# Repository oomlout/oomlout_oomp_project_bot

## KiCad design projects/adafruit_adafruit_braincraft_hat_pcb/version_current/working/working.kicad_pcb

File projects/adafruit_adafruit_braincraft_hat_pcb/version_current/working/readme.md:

# OOMP Project  
## Adafruit-BrainCraft-HAT-PCB  by adafruit  
  
oomp key: oomp_projects_flat_adafruit_adafruit_braincraft_hat_pcb  
(snippet of original readme)  
  
-- Adafruit Adafruit BrainCraft HAT - Machine Learning for Raspberry Pi 4 PCB  
  
<a href="http://www.adafruit.com/products/4374"><br/>  
Click here to purchase one from the Adafruit shop</a>  
  
PCB files for the Adafruit BrainCraft HAT - Machine Learning for Raspberry Pi 4.   
  
Format is EagleCAD schematic and board layout  
* https://www.adafruit.com/product/4374  
  
--- Description  
  
The idea behind the BrainCraft HAT is that you’d be able to “craft brains” for Machine Learning on the EDGE, with Microcontrollers & Microcomputers. On ASK AN ENGINEER, our founder & engineer chatted with Pete Warden, the technical lead of the mobile, embedded TensorFlow Group on Google’s Brain team about what would be ideal for a board like this.  
  
And here’s what we designed! The BrainCraft HAT has a 240×240 TFT IPS display for inference output, slots for camera connector cable for imaging projects, a 5 way joystick and button for UI input, left and right microphones, stereo headphone out, stereo 1 W speaker out, three RGB DotStar LEDs, two 3 pin STEMMA connectors on PWM pins so they can drive NeoPixels or servos, and Grove/STEMMA/Qwiic I2C port. This will let people build a wide range of audio/video AI projects while also allowing easy plug-in of sensors and robotics!  
  
A controllable mini fan attaches to the bottom, and can be used to keep your Pi cool while doing intense AI inference calculations. **Most importantly, there’s an On/Off switch that will comp  
  full source readme at [readme_src.md](readme_src.md)  
  
source repo at: [https://github.com/adafruit/Adafruit-BrainCraft-HAT-PCB](https://github.com/adafruit/Adafruit-BrainCraft-HAT-PCB)  
## Board  

## Schematic  

[schematic pdf](working_schematic.pdf)  
## Images

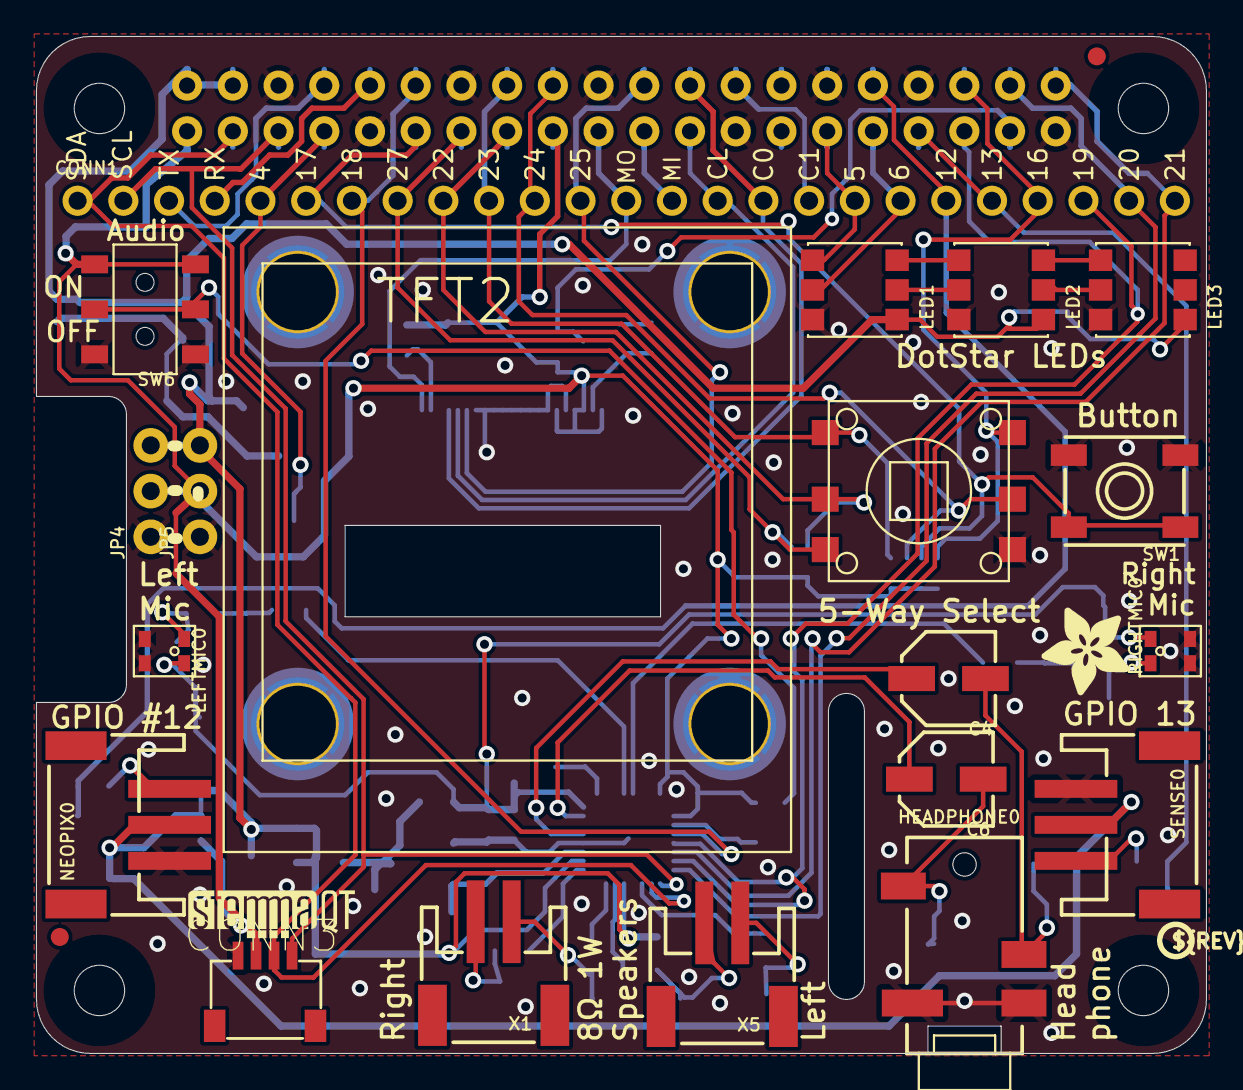
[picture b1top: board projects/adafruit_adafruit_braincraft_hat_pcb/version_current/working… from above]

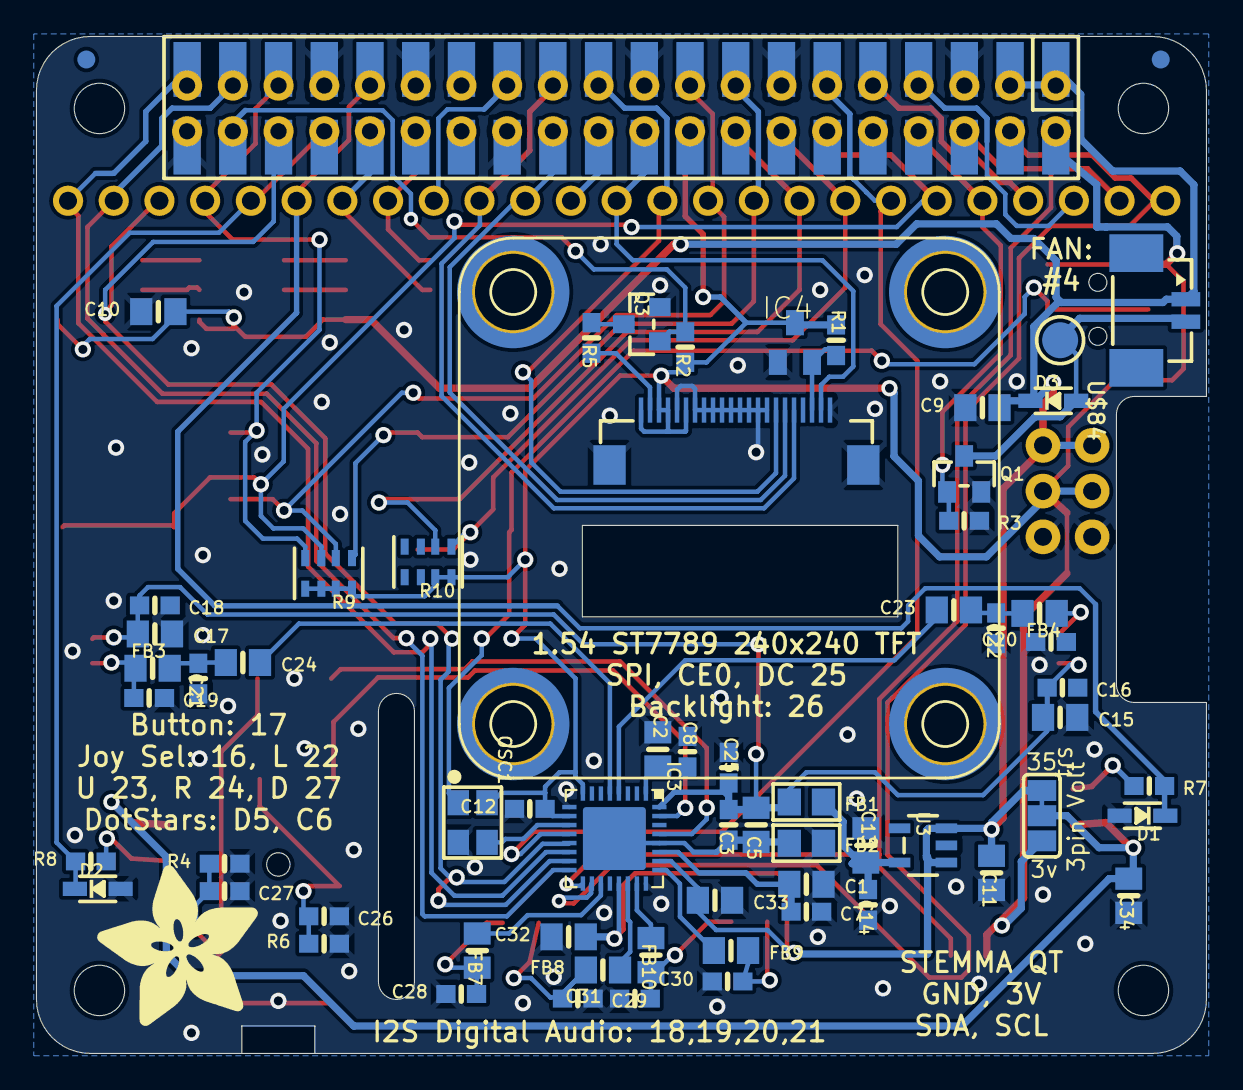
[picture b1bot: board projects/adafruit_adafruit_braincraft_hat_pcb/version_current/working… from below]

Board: 2 copper layers, 65.0 x 56.5 mm, 95 parts (69 on the bottom side), 67 nets.

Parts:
C1, C2, C5, C9, C10, C11, C13, C15, C17, C23, C24, C32, C33, C34: 10uF; 0805-NO
C3, C7, C8, C12, C14, C16, C18, C25: 0.1uF; 0603-NO
C4, C6: 100uF; PANASONIC_C
C19, C20, C21, C22: 33pF; 0603-NO
C26, C27: 220pF; 0603-NO
C28, C29, C30, C31: 100pF; 0603-NO
CONN1: HEADER-1X25; 1X25_ROUND_70MIL
CONN3: STEMMA_I2C_QT; JST_SH4
D1, D2: 3.6V; SOD-323
D3: 1N4148; SOD-323
FB1, FB2: Ferrite; 0805
FB3, FB7, FB8, FB9, FB10: Ferrite; 0805-NO
FB4: FERRITE; 0805-NO
FID1, FID2: FIDUCIAL_1MM
HEADPHONE0: 4UCONN_18510
IC3: WM8960; QFN32_5MM
IC4: APX803-SAG; SOT23
JP4, JP5: 1X03_ROUND_76
LED1, LED2, LED3: SK6822; APA102
LEFTMIC0: SPW2430HR5H-B
NEOPIX0: JST PH 3; JSTPH3
OSC1: ECS-3225MV; OSC_3.2X2.5MM
Q1, Q3: BSS138; SOT23-WIDE
R1, R2, R3, R4: 10K; 0603-NO
R5: 10; 0603-NO
R6: 10k; 0603-NO
R7, R8: 1K; 0603-NO
R9, R10: 10K; RESPACK_4X0603
RIGHTMIC0: SPW2430HR5H-B
RPI1: RASPBERRYPI_BPLUS_HAT_SMTTHM_SLOTS; PI_HAT_SMTTHM_SLOTS
SENSE0: JST PH 3; JSTPH3
SJ1: SOLDERJUMPER_2WAY_OPEN_NOPASTE
SW1: EVQQ; EVQ-Q2_SMALLER
SW5: NAVSWITCHSKQUABAUE010; SKQUBAE010
SW6: EG1390
TFT2: DISP_TFT_1.54IN_240X240_22P; TFT_1.54IN_240X240_22PIN
TP1, TP2, TP3, TP4: SEWTAP_SMTNUTM3; SMT_NUT_3MM
TP6: TESTPOINT_ROUND_2MM
U3: AP2112-3.3K; SOT23-5
U$11: PCBFEAT-REV-040
U$72: STEMMAQT
U$75: ADAFRUIT_5MM
U$79: BRAINPAD_1IN
U$82: FAN_30X30MM
U$84: CON_MOLEX_2P; 53398-0271
U$87: ADAFRUIT_9MM
X1, X5: JSTPH 2P; JSTPH2

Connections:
3.3V: C12.1, CONN3.2, IC3.8, IC3.10, IC4.3, JP4.2, JP5.2, OSC1.4, R1.2, R2.2, R9.5, R9.6, R9.7, R9.8, R10.7, R10.8, RPI1.1, RPI1.17, RPI1.S1, RPI1.S17, SJ1.3, SW6.S1, SW6.S2, TFT2.1, TFT2.3, TFT2.4, TFT2.6
5.0V: C9.1, C10.1, C11.1, C32.1, C33.1, D3.C, IC3.21, IC3.26, JP4.3, JP5.3, LED1.4, LED2.4, LED3.4, RPI1.2, RPI1.4, RPI1.S2, RPI1.S4, SJ1.1, U3.1, U3.3, U$84.1
AGND: C3.2, C5.2, FB2.1, IC3.28, IC3.33
AVDD: C3.1, C5.1, C15.1, C16.1, C17.1, C18.1, C25.1, FB1.1, IC3.32, LEFTMIC0.4, RIGHTMIC0.4
BUTTON: CONN1.6, R9.3, RPI1.11, RPI1.S11, SW1.B, SW1.B'
EECLK: RPI1.28, RPI1.S28
EEDATA: RPI1.27, RPI1.S27
FAN: CONN1.5, Q1.1, R3.1, RPI1.7, RPI1.S7
GND: C1.2, C2.2, C7.2, C8.2, C9.2, C10.2, C11.2, C12.2, C13.2, C14.2, C15.2, C16.2, C17.2, C18.2, C19.2, C20.2, C21.2, C22.2, C25.2, C26.2, C27.2, C28.2, C29.2, C30.2, C31.2, C32.2, C33.2, C34.2, CONN3.1, D1.A, D2.A, FB2.2, HEADPHONE0.1-GND, HEADPHONE0.4-INNER_SLEEVE, IC3.9, IC3.20, IC3.24, IC4.1, JP4.1, JP5.1, LED1.3, LED2.3, LED3.3, LEFTMIC0.2, LEFTMIC0.3, NEOPIX0.1, OSC1.2, Q1.2, Q3.2, R3.2, R4.1, R6.1, RIGHTMIC0.2, RIGHTMIC0.3, RPI1.6, RPI1.9, RPI1.14, RPI1.20, RPI1.25, RPI1.30, RPI1.34, RPI1.39, RPI1.S6, RPI1.S9, RPI1.S14, RPI1.S20, RPI1.S25, RPI1.S30, RPI1.S34, RPI1.S39, SENSE0.1, SW1.A, SW1.A', SW5.4, SW6.O1, SW6.O2, TFT2.5, TFT2.7, TFT2.8, TFT2.9, TFT2.10, TFT2.11, TFT2.12, TFT2.13, TFT2.14, TFT2.15, TFT2.22, TFT2.SUPPORT1, TFT2.SUPPORT2, TP1.P$1, TP2.P$1, TP3.P$1, TP4.P$1, U3.2
I2S_BCLK: CONN1.7, IC3.12, RPI1.12, RPI1.S12
I2S_DIN: CONN1.24, IC3.16, RPI1.38, RPI1.S38
I2S_DOUT: CONN1.25, IC3.14, RPI1.40, RPI1.S40
I2S_LRCLK: CONN1.23, IC3.13, IC3.15, RPI1.35, RPI1.S35
JOY_D: CONN1.8, R10.1, RPI1.13, RPI1.S13, SW5.3
JOY_IN: CONN1.22, R9.4, RPI1.36, RPI1.S36, SW5.6
JOY_L: CONN1.9, R10.2, RPI1.15, RPI1.S15, SW5.2
JOY_R: CONN1.11, R9.2, RPI1.18, RPI1.S18, SW5.5
JOY_U: CONN1.10, R9.1, RPI1.16, RPI1.S16, SW5.1
LEDC: CONN1.19, LED1.2, RPI1.31, RPI1.S31
LEDD: CONN1.18, LED1.1, RPI1.29, RPI1.S29
LEDK: R5.2, TFT2.2
LINPUT1: C23.2, IC3.4
LITE: Q3.1, R2.1, RPI1.37, RPI1.S37
LSTEMMA: NEOPIX0.3, R7.1
MCLK: IC3.11, OSC1.3
MCLK_EN: OSC1.1, SW6.P1, SW6.P2
MICBIAS: C2.1, C8.1, IC3.1
unnamed: FB7.1, IC3.19
unnamed: FB8.1, IC3.22
unnamed: C6.+, IC3.31
unnamed: Q3.3, R5.1
unnamed: C4.+, IC3.29
unnamed: LED1.6, LED2.1
unnamed: C4.-, C27.1, HEADPHONE0.3-OUTER_SLEEVE, R4.2
unnamed: C6.-, C26.1, HEADPHONE0.2-TIP, R6.2
unnamed: LED1.5, LED2.2
unnamed: C19.1, FB3.1, RIGHTMIC0.1
unnamed: C20.1, FB4.1, LEFTMIC0.1
unnamed: LED2.6, LED3.1
unnamed: LED2.5, LED3.2
unnamed: C21.1, C24.1, FB3.2
unnamed: C22.1, C23.1, FB4.2
unnamed: D3.A, Q1.3, TP6.P$1, U$84.2
unnamed: FB9.1, IC3.25
unnamed: FB10.1, IC3.23
OUT: C13.1, C14.1, FB1.2, U3.5
PWM0: CONN1.20, D1.C, R7.2, RPI1.32, RPI1.S32
PWM1: CONN1.21, D2.C, R8.2, RPI1.33, RPI1.S33
RINPUT1: C24.2, IC3.5
RSTEMMA: R8.1, SENSE0.3
RXD: CONN1.4, RPI1.10, RPI1.S10
SCL: CONN1.2, CONN3.4, IC3.17, RPI1.5, RPI1.S5
SDA: CONN1.1, CONN3.3, IC3.18, RPI1.3, RPI1.S3
SPI_CE1: CONN1.17, RPI1.26, RPI1.S26
SPI_MISO: CONN1.14, RPI1.21, RPI1.S21
SPK_LN: C31.1, FB10.2, X1.1
SPK_LP: C30.1, FB9.2, X1.2
SPK_RN: C28.1, FB7.2, X5.1
SPK_RP: C29.1, FB8.2, X5.2
TFT_CS: CONN1.16, RPI1.24, RPI1.S24, TFT2.18
TFT_DC: CONN1.12, RPI1.22, RPI1.S22, TFT2.16
TFT_MOSI: CONN1.13, RPI1.19, RPI1.S19, TFT2.21
TFT_RESET: IC4.2, R1.1, TFT2.20
TFT_SCLK: CONN1.15, RPI1.23, RPI1.S23, TFT2.17
TXD: CONN1.3, RPI1.8, RPI1.S8
VCC: C34.1, NEOPIX0.2, SENSE0.2, SJ1.2
VMID: C1.1, C7.1, IC3.27

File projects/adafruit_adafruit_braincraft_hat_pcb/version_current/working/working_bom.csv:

"Id";"Designator";"Footprint";"Quantity";"Designation";"Supplier and ref";
1;"FID2,FID1";"FIDUCIAL_1MM";2;"FIDUCIAL_1MM";;;
2;"LED1,LED3,LED2";"APA102";3;"SK6822";;;
3;"JP4,JP5";"1X03_ROUND_76";2;"";;;
4;"TFT2";"TFT_1.54IN_240X240_22PIN";1;"DISP_TFT_1.54IN_240X240_22P";;;
5;"SW5";"SKQUBAE010";1;"NAVSWITCHSKQUABAUE010";;;
6;"NEOPIX0,SENSE0";"JSTPH3";2;"JST PH 3";;;
7;"X1,X5";"JSTPH2";2;"JSTPH 2P";;;
8;"C4,C6";"PANASONIC_C";2;"100uF";;;
9;"CONN1";"1X25_ROUND_70MIL";1;"HEADER-1X25";;;
10;"HEADPHONE0";"4UCONN_18510";1;"";;;
11;"SW1";"EVQ-Q2_SMALLER";1;"EVQQ";;;
12;"LEFTMIC0,RIGHTMIC0";"SPW2430HR5H-B";2;"";;;
13;"U$11";"PCBFEAT-REV-040";1;"";;;
14;"U$75";"ADAFRUIT_5MM";1;"";;;
15;"SW6";"EG1390";1;"EG1390";;;
16;"RPI1";"PI_HAT_SMTTHM_SLOTS";1;"RASPBERRYPI_BPLUS_HAT_SMTTHM_SLOTS";;;
17;"U$72";"STEMMAQT";1;"";;;
18;"CONN3";"JST_SH4";1;"STEMMA_I2C_QT";;;
19;"C32,C17,C5,C15,C24,C9,C2,C33,C23,C11,C1,C10,C34,C13";"0805-NO";14;"10uF";;;
20;"U$87";"ADAFRUIT_9MM";1;"";;;
21;"R10,R9";"RESPACK_4X0603";2;"10K";;;
22;"OSC1";"OSC_3.2X2.5MM";1;"ECS-3225MV";;;
23;"C20,C21,C22,C19";"0603-NO";4;"33pF";;;
24;"C30,C28,C29,C31";"0603-NO";4;"100pF";;;
25;"FB10,FB7,FB8,FB3,FB9";"0805-NO";5;"Ferrite";;;
26;"FB2,FB1";"0805";2;"Ferrite";;;
27;"D3";"SOD-323";1;"1N4148";;;
28;"C14,C8,C25,C16,C12,C7,C18,C3";"0603-NO";8;"0.1uF";;;
29;"TP3,TP1,TP2,TP4";"SMT_NUT_3MM";4;"SEWTAP_SMTNUTM3";;;
30;"R6";"0603-NO";1;"10k";;;
31;"Q3,Q1";"SOT23-WIDE";2;"BSS138";;;
32;"R4,R1,R2,R3";"0603-NO";4;"10K";;;
33;"D1,D2";"SOD-323";2;"3.6V";;;
34;"C26,C27";"0603-NO";2;"220pF";;;
35;"IC3";"QFN32_5MM";1;"WM8960";;;
36;"R5";"0603-NO";1;"10";;;
37;"U$79";"BRAINPAD_1IN";1;"";;;
38;"FB4";"0805-NO";1;"FERRITE";;;
39;"IC4";"SOT23";1;"APX803-SAG";;;
40;"SJ1";"SOLDERJUMPER_2WAY_OPEN_NOPASTE";1;"";;;
41;"U$82";"FAN_30X30MM";1;"";;;
42;"U3";"SOT23-5";1;"AP2112-3.3K";;;
43;"TP6";"TESTPOINT_ROUND_2MM";1;"";;;
44;"R8,R7";"0603-NO";2;"1K";;;
45;"U$84";"53398-0271";1;"CON_MOLEX_2P";;;

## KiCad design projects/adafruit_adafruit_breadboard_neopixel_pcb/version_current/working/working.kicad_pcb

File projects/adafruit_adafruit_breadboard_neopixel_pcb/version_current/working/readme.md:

# Adafruit_Breadboard_NeoPixel_PCB by adafruit  
This is a harvested standardized copy of a project from github.  
The original project can be found at:  
https://github.com/adafruit/Adafruit_Breadboard_NeoPixel_PCB  
Please consult that link for additional, details, files, and license information.  
Note: It was auto harvested and if the original repo had more than one board file or anything out of the ordinary the files here are likely not representative.

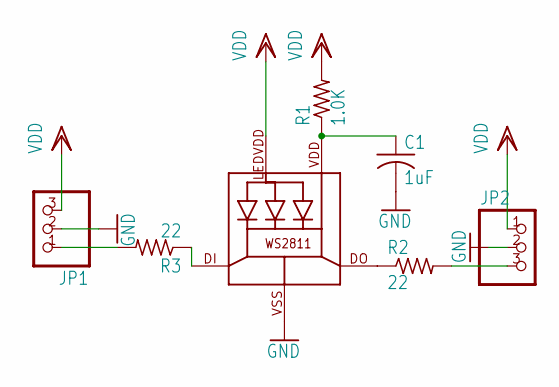
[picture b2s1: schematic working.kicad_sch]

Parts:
C1: 1uF; C0603K
JP1, JP2: PINHD-1X3CB; 1X03-CLEANBIG
LED1: WS28115050
R1: 1.0K; R0603
R2, R3: 22; R0603

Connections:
GND: C1.2, JP1.2, JP2.2, LED1.VSS (GND)
IN: JP1.1, R3.2
unnamed: LED1.DO, R2.1
unnamed: LED1.DI, R3.1
unnamed: C1.1, LED1.VDD, R1.1
OUT: JP2.3, R2.2
VDD: JP1.3, JP2.1, LED1.LEDVDD, R1.2

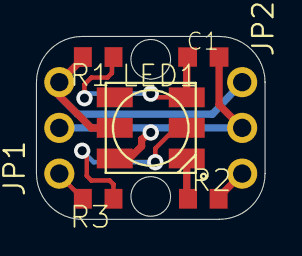
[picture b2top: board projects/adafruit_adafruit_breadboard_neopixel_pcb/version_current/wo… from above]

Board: 16 copper layers, 12.7 x 10.2 mm, 10 parts (1 on the bottom side), 7 nets.

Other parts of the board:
@HOLE0, @HOLE1: (no value)
U$1: ADAFRUIT_2.5MM

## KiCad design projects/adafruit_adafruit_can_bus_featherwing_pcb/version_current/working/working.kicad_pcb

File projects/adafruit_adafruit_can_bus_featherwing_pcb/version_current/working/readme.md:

# Adafruit-CAN-Bus-FeatherWing-PCB by adafruit  
This is a harvested standardized copy of a project from github.  
The original project can be found at:  
https://github.com/adafruit/Adafruit-CAN-Bus-FeatherWing-PCB  
Please consult that link for additional, details, files, and license information.  
Note: It was auto harvested and if the original repo had more than one board file or anything out of the ordinary the files here are likely not representative.

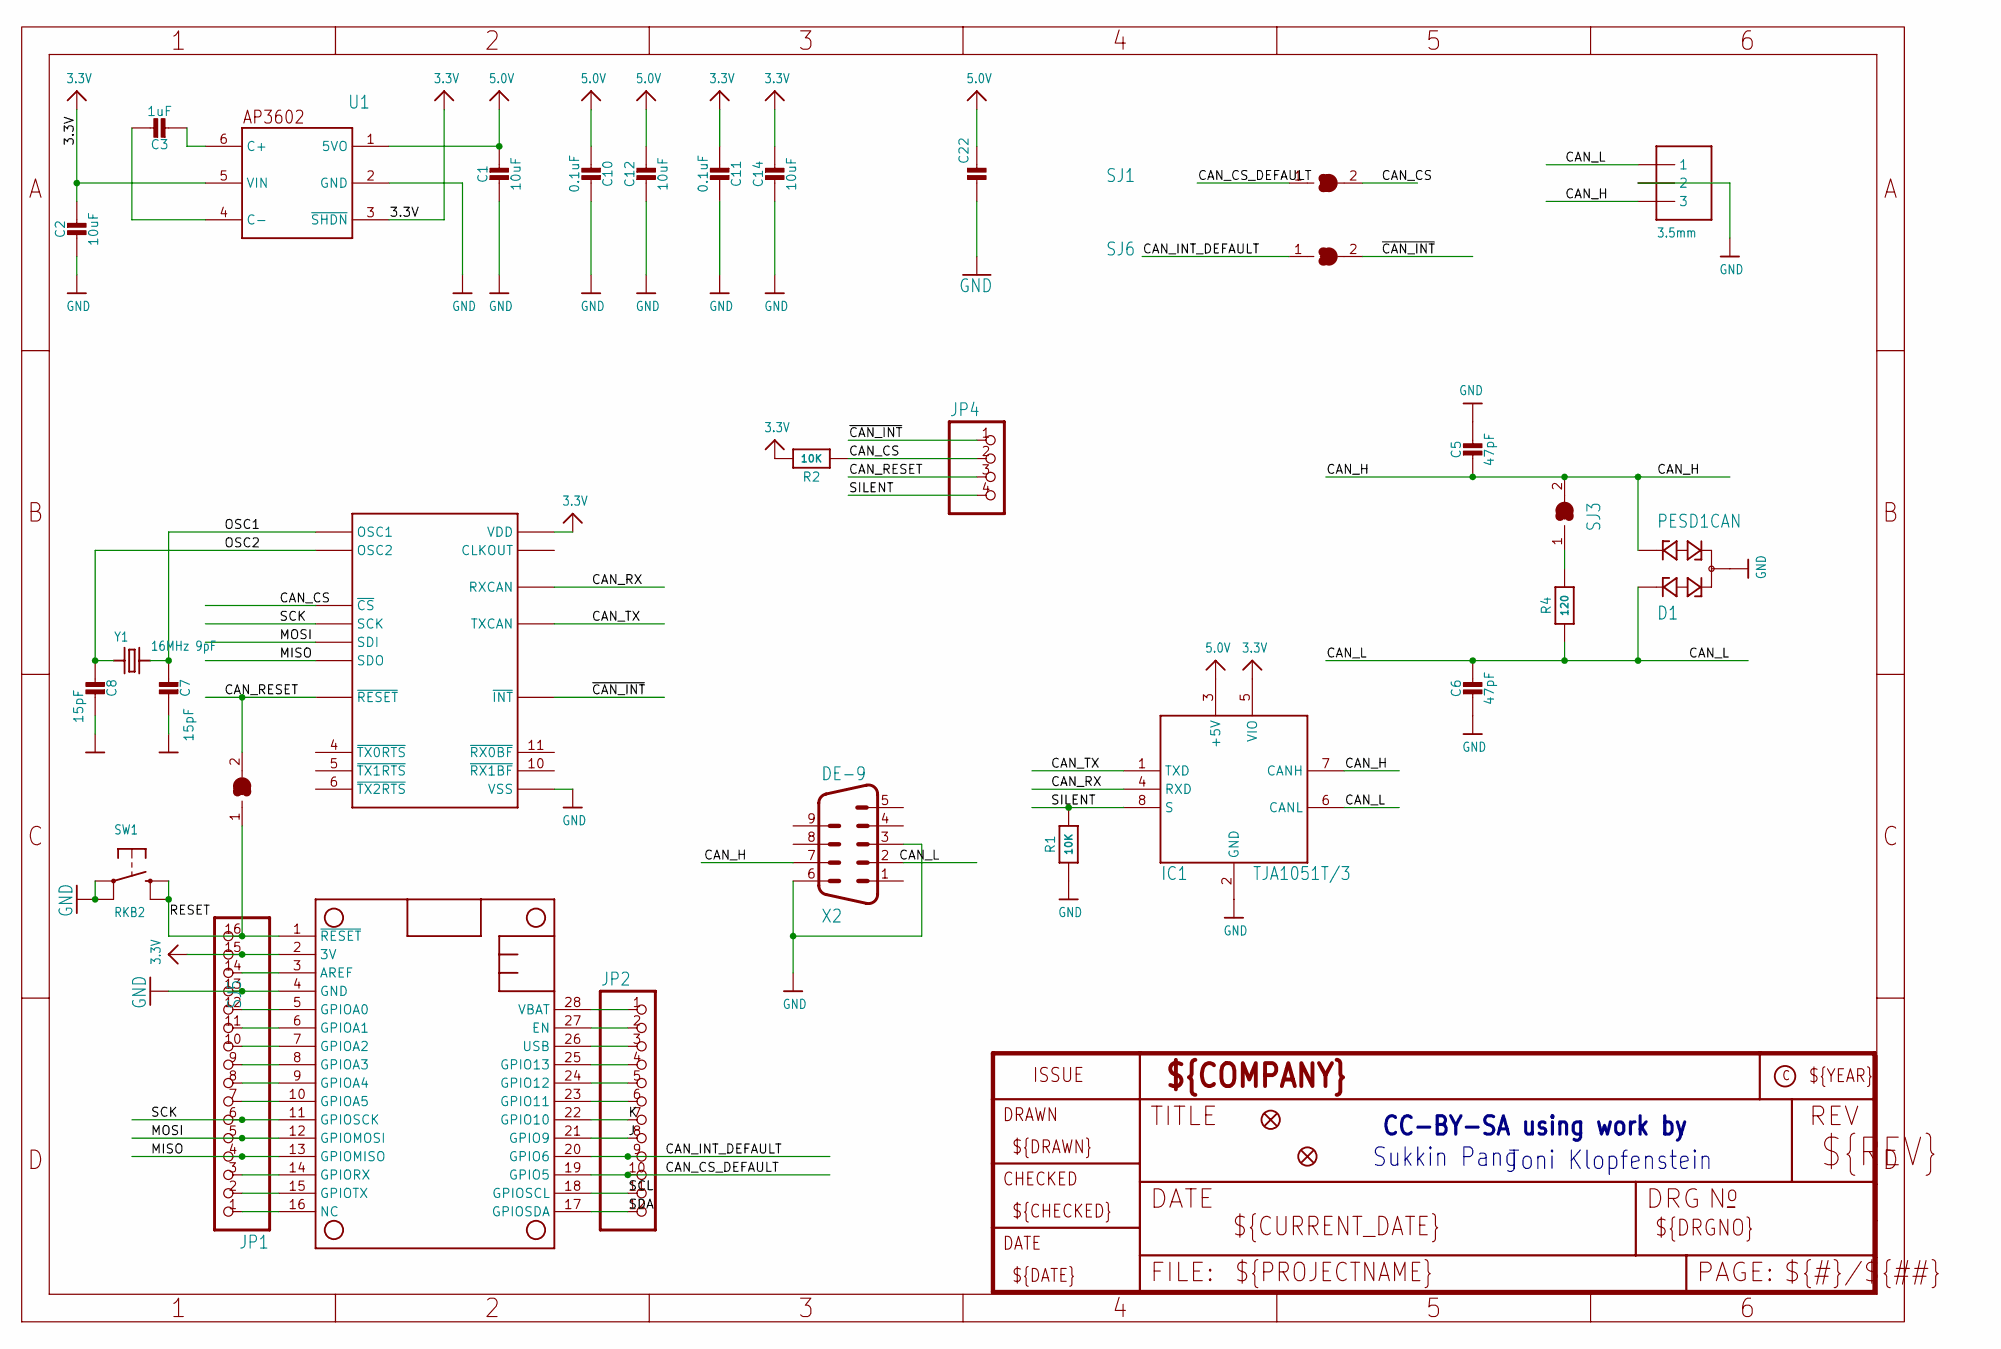
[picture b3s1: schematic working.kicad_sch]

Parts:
C1, C2, C12, C14: 10uF; 0805-NO
C3: 1uF; 0805-NO
C5, C6: 47pF; 0603-NO
C7, C8: 15pF; 0603-NO
C10, C11, C22: 0.1uF; 0603-NO
D1: PESD1CAN; SOT23
FID2, FID3: FIDUCIAL_1MM
IC1: TJA1051T/3; SOIC8_150MIL
IC2: MCP2515/SO; SOIC18WIDE
JP1: HEADER-1X16ROUND; 1X16_ROUND
JP2: HEADER-1X12; 1X12_ROUND
JP4: HEADER-1X4ROUND; 1X04_ROUND
MS1: FEATHERWING_NODIM
NEOPIX1: 3.5mm; TERMBLOCK_1X3-3.5MM
R1, R2: 10K; 0603-NO
R4: 120; 0603-NO
SJ1, SJ3, SJ5, SJ6: SOLDERJUMPER_CLOSED; SOLDERJUMPER_CLOSEDWIRE
SW1: RKB2; BTN_RKB2_4.6X2.8
U1: AP3602; SOT23-6
X2: DE-9; M09D
Y1: 16MHz 9pF; CRYSTAL_3.2X2.5

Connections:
3.3V: C2.1, C11.2, C14.1, IC1.5 (VIO), IC2.18 (VDD), JP1.15, MS1.2 (3V), R2.2, U1.3 (~SHDN), U1.5 (VIN)
5.0V: C1.1, C10.2, C12.1, C22.2, IC1.3 (+5V), U1.1 (5VO)
A: JP1.12, MS1.5 (GPIOA0)
AREF: JP1.14, MS1.3 (AREF)
B: JP1.11, MS1.6 (GPIOA1)
C: JP1.10, MS1.7 (GPIOA2)
CAN_CS: IC2.16 (~CS), JP4.2, R2.1, SJ1.2
CAN_CS_DEFAULT: JP2.10, MS1.19 (GPIO5), SJ1.1
CAN_H: C5.2, D1.2, IC1.7 (CANH), NEOPIX1.3, SJ3.2, X2.7
CAN_INT_DEFAULT: JP2.9, MS1.20 (GPIO6), SJ6.1
CAN_L: C6.1, D1.1, IC1.6 (CANL), NEOPIX1.1, R4.1, X2.2
CAN_RESET: IC2.17 (~RESET), JP4.3, SJ5.2
CAN_RX: IC1.4 (RXD), IC2.2 (RXCAN)
CAN_TX: IC1.1 (TXD), IC2.1 (TXCAN)
D: JP1.9, MS1.8 (GPIOA3)
E: JP1.8, MS1.9 (GPIOA4)
EN: JP2.2, MS1.27 (EN)
F: JP1.7, MS1.10 (GPIOA5)
G: JP1.1, MS1.16 (NC)
GND: C1.2, C2.2, C5.1, C6.2, C7.1, C8.1, C10.1, C11.1, C12.2, C14.2, C22.1, D1.3, IC1.2 (GND), IC2.9 (VSS), JP1.13, MS1.4 (GND), NEOPIX1.2, R1.1, SW1.A, SW1.A' (P1), U1.2 (GND), X2.3, X2.6
J: JP2.8, MS1.21 (GPIO9)
K: JP2.7, MS1.22 (GPIO10)
L: JP2.6, MS1.23 (GPIO11)
M: JP2.5, MS1.24 (GPIO12)
MISO: IC2.15 (SDO), JP1.4, MS1.13 (GPIOMISO)
MOSI: IC2.14 (SDI), JP1.5, MS1.12 (GPIOMOSI)
N: JP2.4, MS1.25 (GPIO13)
unnamed: C3.2, U1.6 (C+)
unnamed: C3.1, U1.4 (C-)
unnamed: R4.2, SJ3.1
OSC1: C7.2, IC2.8 (OSC1), Y1.2
OSC2: C8.2, IC2.7 (OSC2), Y1.1
RESET: JP1.16, MS1.1 (~RESET), SJ5.1, SW1.B (S), SW1.B' (S1)
RX: JP1.3, MS1.14 (GPIORX)
SCK: IC2.13 (SCK), JP1.6, MS1.11 (GPIOSCK)
SCL: JP2.11, MS1.18 (GPIOSCL)
SDA: JP2.12, MS1.17 (GPIOSDA)
SILENT: IC1.8 (S), JP4.4, R1.2
TX: JP1.2, MS1.15 (GPIOTX)
USB: JP2.3, MS1.26 (USB)
VBAT: JP2.1, MS1.28 (VBAT)
~CAN_INT: IC2.12 (~INT), JP4.1, SJ6.2

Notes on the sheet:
Sukkin Pang
CC-BY-SA using work by
Toni Klopfenstein

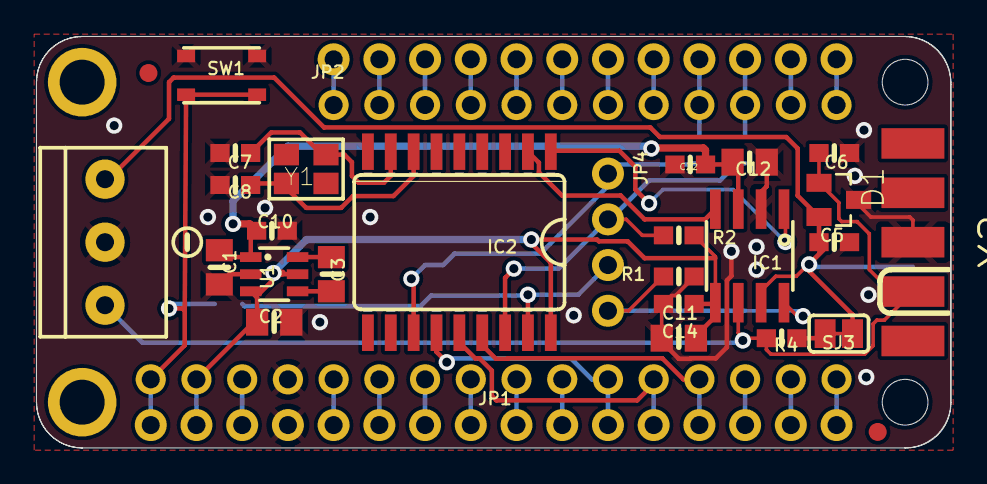
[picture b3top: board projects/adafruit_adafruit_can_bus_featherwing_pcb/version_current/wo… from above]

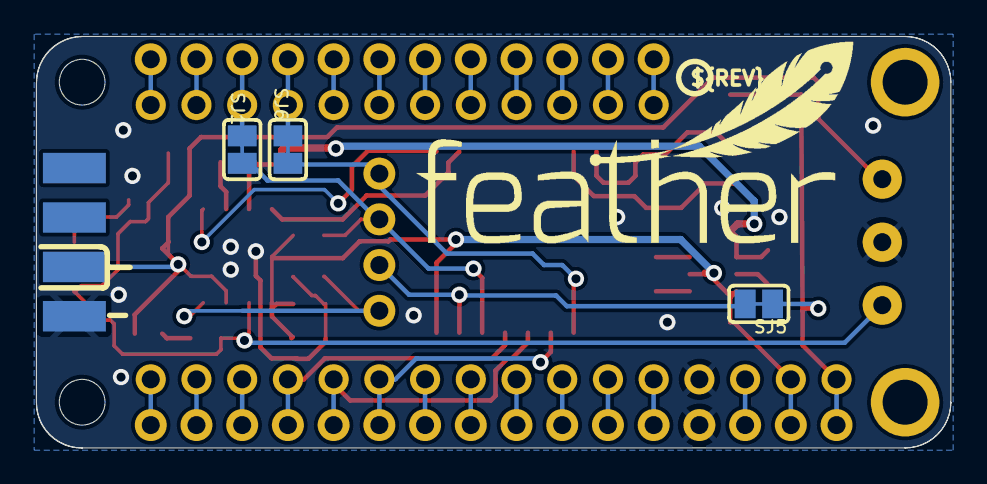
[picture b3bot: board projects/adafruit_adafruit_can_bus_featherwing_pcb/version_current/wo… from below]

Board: 16 copper layers, 50.8 x 22.9 mm, 52 parts (12 on the bottom side), 42 nets.

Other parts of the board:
PLABEL0: PLABEL0
PLABEL1: PLABEL1
PLABEL2: PLABEL2
PLABEL3: PLABEL3
PLABEL4: PLABEL4
PLABEL5: PLABEL5
PLABEL6: PLABEL6
PLABEL8: PLABEL8
PLABEL9: PLABEL9
PLABEL10: PLABEL10
PLABEL11: PLABEL11
PLABEL12: PLABEL12
PLABEL13: PLABEL13
PLABEL14: PLABEL14
PLABEL15: PLABEL15
PLABEL16: PLABEL16
U$21: SYMBOL_MINUS
U$22: FEATHERLOGO
U$33: PCBFEAT-REV-040

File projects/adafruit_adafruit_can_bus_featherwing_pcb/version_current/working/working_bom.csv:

Row,Description,Part,References,Value,Footprint,Quantity Per PCB,Status,Datasheet
1,,CAP_CERAMIC0603_NO,C7 C8,15pF,0603-NO,2, ,
2,,CAP_CERAMIC0603_NO,C5 C6,47pF,0603-NO,2, ,
3,,CAP_CERAMIC0603_NO,C10 C11 C22,0.1uF,0603-NO,3, ,
4,,CAP_CERAMIC0805-NOOUTLINE,C3,1uF,0805-NO,1, ,
5,,CAP_CERAMIC0805-NOOUTLINE,C1 C2 C12 C14,10uF,0805-NO,4, ,
6,,PESD1CAN,D1,PESD1CAN,SOT23,1, ,
7,,MCP2515/SO,IC2,MCP2515/SO,SOIC18WIDE,1, ,
8,,CAN_TRANSCIEVER_TCAN1051V,IC1,TJA1051T/3,SOIC8_150MIL,1, ,
9,,HEADER-1X12,JP2,HEADER-1X12,1X12_ROUND,1, ,
10,,HEADER-1X16ROUND,JP1,HEADER-1X16ROUND,1X16_ROUND,1, ,
11,,HEADER-1X4ROUND,JP4,HEADER-1X4ROUND,1X04_ROUND,1, ,
12,,FEATHERWING_NODIM,MS1,FEATHERWING_NODIM,FEATHERWING_NODIM,1, ,
13,,TERMBLOCK_1X3,NEOPIX1,3.5mm,TERMBLOCK_1X3-3.5MM,1, ,
14,,RESISTOR_0603_NOOUT,R4,120,0603-NO,1, ,
15,,RESISTOR_0603_NOOUT,R1 R2,10K,0603-NO,2, ,
16,,SWITCH_TACT_SMT_RKB2,SW1,RKB2,BTN_RKB2_4.6X2.8,1, ,
17,,AP3602,U1,AP3602,SOT23-6,1, ,
18,,M09D,X2,DE-9,M09D,1, ,
19,,CRYSTAL3.2X2.5,Y1,16MHz 9pF,CRYSTAL_3.2X2.5,1, ,





Project info:
Schematic:,working
Variant:,default
Revision:,
Date:,2023-08-02_17-08-32
KiCad Version:,7.0.6-7.0.6~ubuntu22.04.1
Statistics:
Component Groups:,19
Component Count:,27 (0 SMD/ 0 THT)
Fitted Components:,27 (0 SMD/ 0 THT)
Number of PCBs:,1
Total Components:,27

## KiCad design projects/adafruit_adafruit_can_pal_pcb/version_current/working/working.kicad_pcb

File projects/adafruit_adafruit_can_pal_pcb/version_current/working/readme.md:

# OOMP Project  
## Adafruit-CAN-Pal-PCB  by adafruit  
  
oomp key: oomp_projects_flat_adafruit_adafruit_can_pal_pcb  
(snippet of original readme)  
  
-- Adafruit CAN Pal - CAN Bus Transciever - TJA1051T/3 PCB  
  
<a href="http://www.adafruit.com/products/5708"><br/>  
Click here to purchase one from the Adafruit shop</a>  
  
PCB files for the Adafruit CAN Pal - CAN Bus Transciever - TJA1051T/3.   
  
Format is EagleCAD schematic and board layout  
* https://www.adafruit.com/product/5708  
  
--- Description  
  
If you'd like to connect a board with native CAN Peripheral support, the Adafruit CAN Pal Transceiver will take the 3V logic level signals and convert them to CAN logic levels with the differential signaling required to communicate. Note that not all chips have a CAN peripheral! Some that we know do have it are the ESP32/ESP32-S2/ESP32-S3 (note that ESP32 calls this interface TWAI not CAN) series of chips, SAME51, STM32F405, or Teensy 4.  
  
Check the product documentation for the board you are wiring this to, to make sure that the chip has CAN support and the RX and TX pins are brought out for you to connect the transceiver to! Despite sharing the 'RX' and 'TX' name with UART, they're not at all the same interface.  
  
CAN Bus is a small-scale networking standard, originally designed for cars and, yes, busses, but is now used for many robotics or sensor networks that need better range and addressing than I2C, and don't have the pins or computational ability to talk on Ethernet. CAN is 2 wire differential, which means it's good for long distances and noisy environments.  
  
Messages are sent at a  
  full source readme at [readme_src.md](readme_src.md)  
  
source repo at: [https://github.com/adafruit/Adafruit-CAN-Pal-PCB](https://github.com/adafruit/Adafruit-CAN-Pal-PCB)  
## Board  

## Schematic  

[schematic pdf](working_schematic.pdf)  
## Images

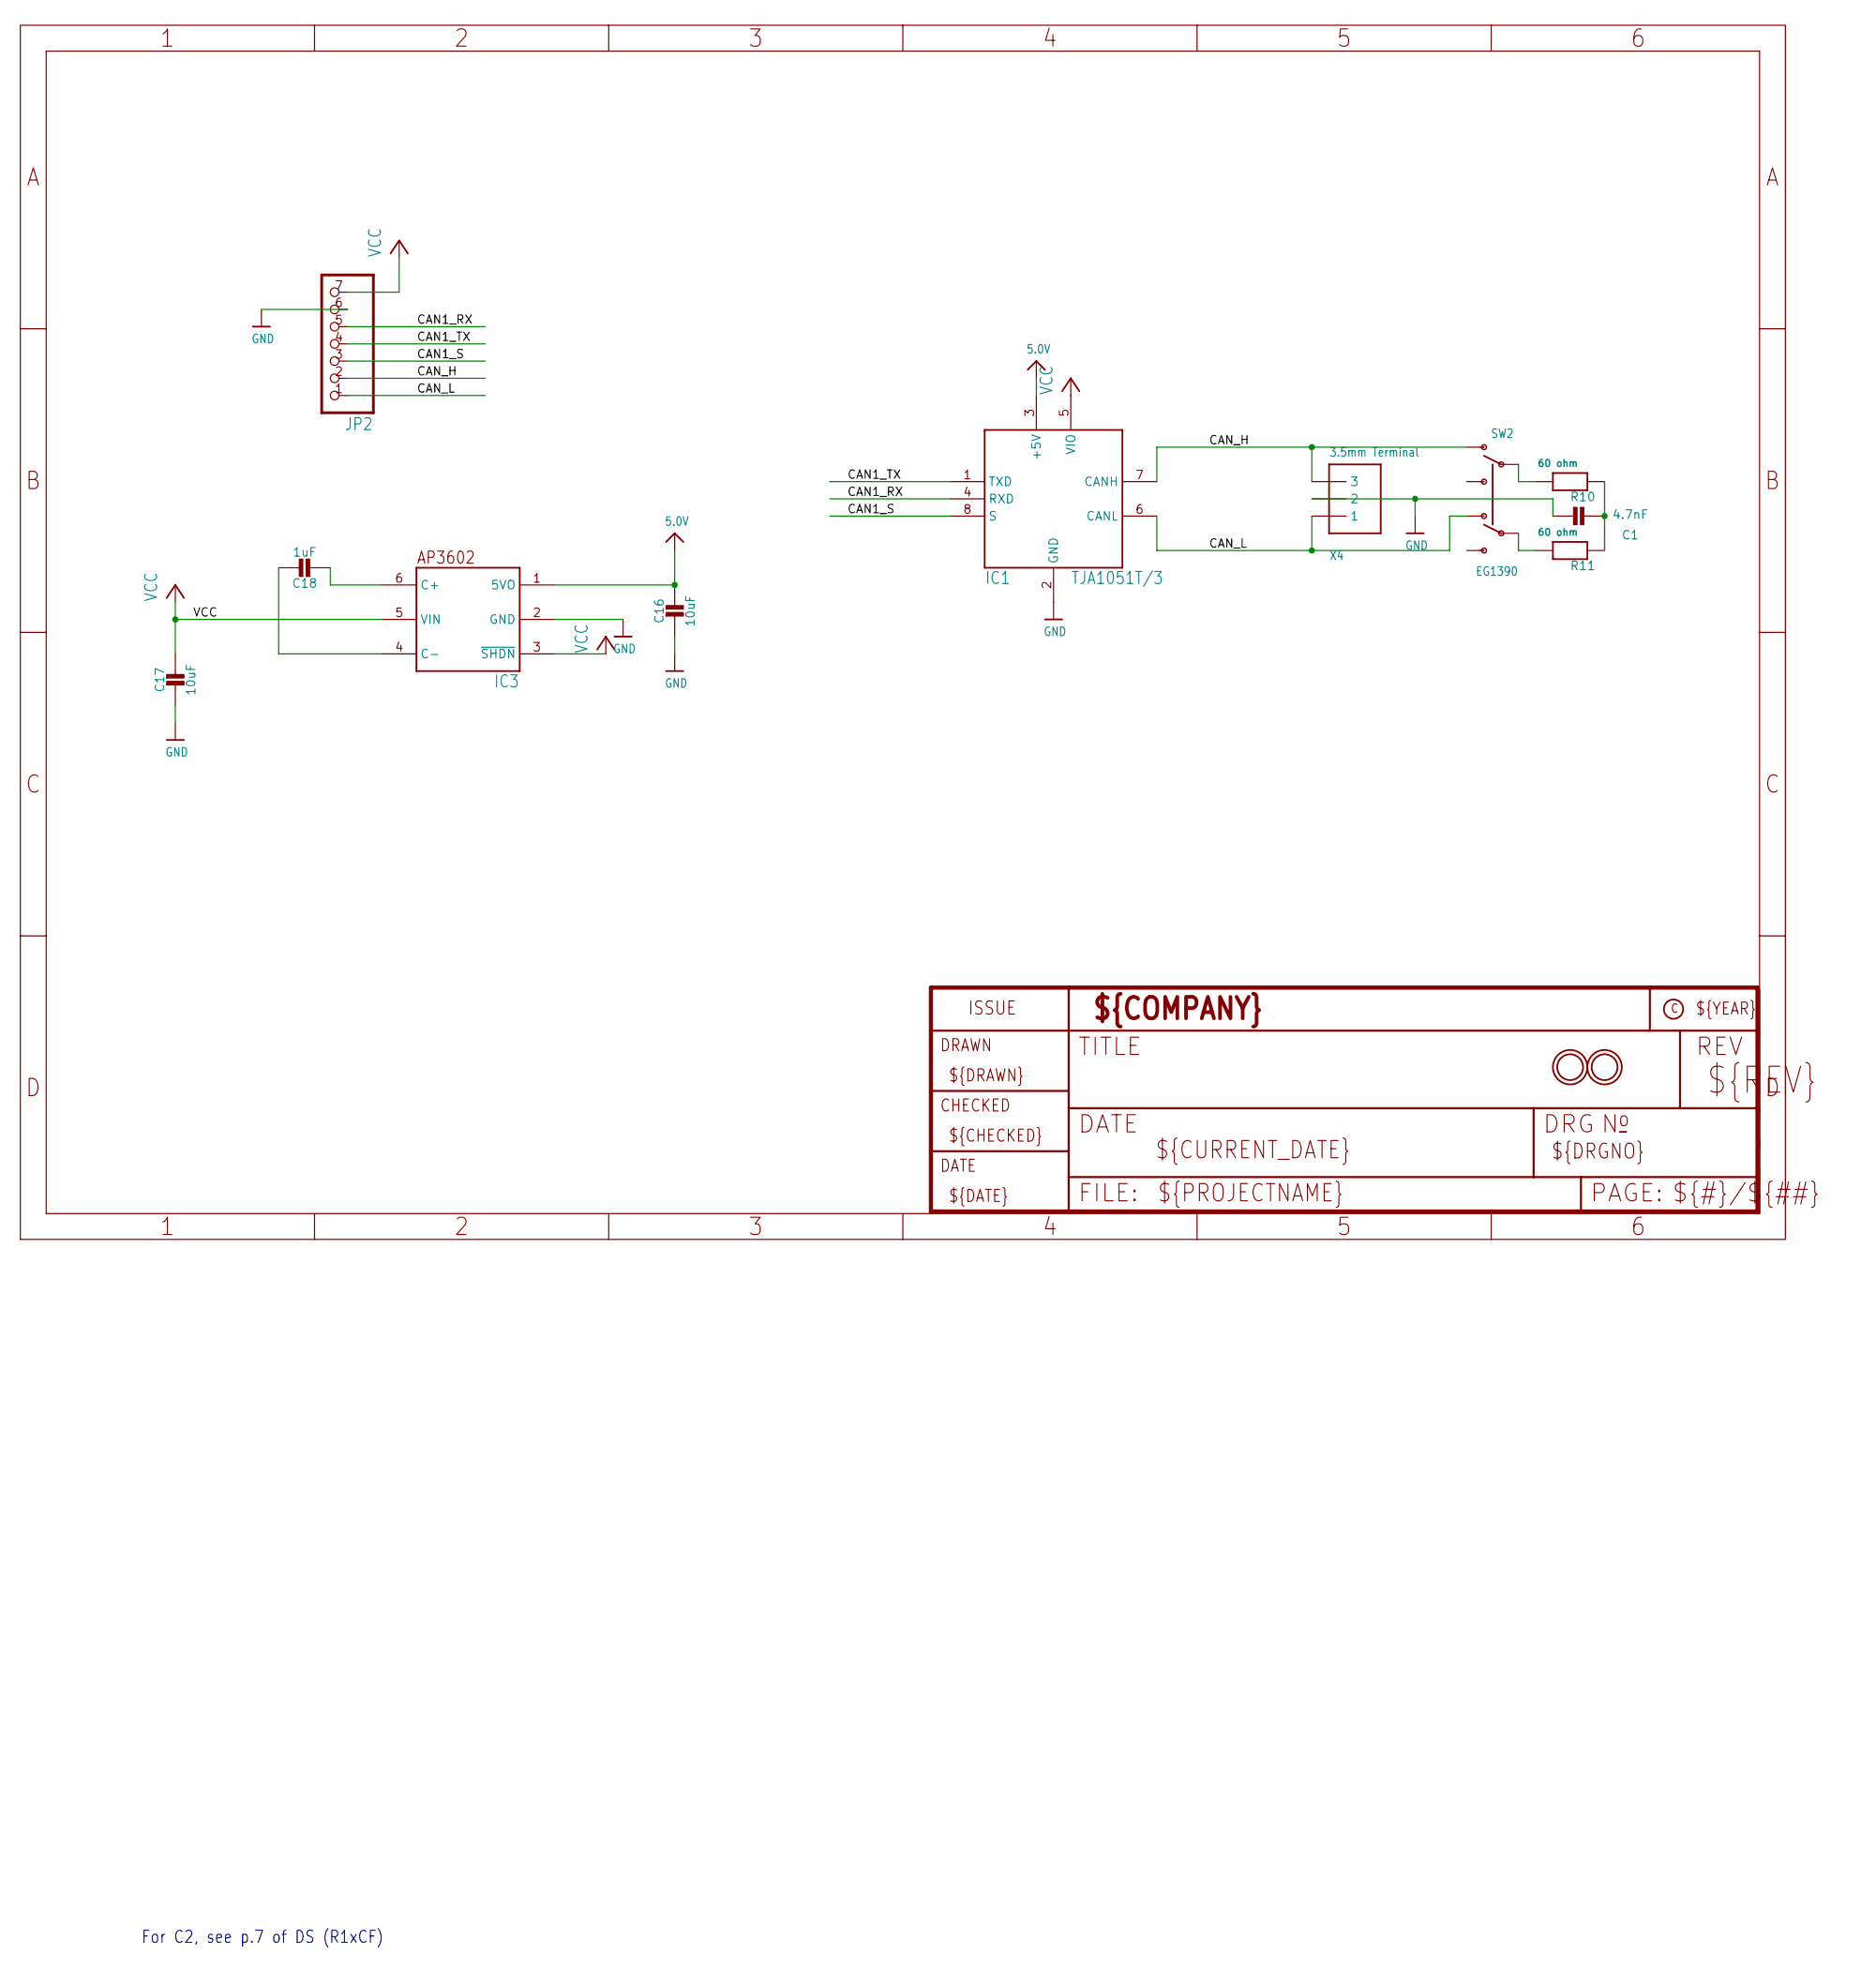
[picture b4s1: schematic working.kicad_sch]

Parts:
C1: 4.7nF; 0603-NO
C16, C17: 10uF; 0805-NO
C18: 1uF; 0805_10MGAP
IC1: TJA1051T/3; SOIC8_150MIL
IC3: AP3602; SOT23-6
JP2: HEADER-1X770MIL; 1X07_ROUND_70
R10, R11: 60 ohm; 0603-NO
SW2: EG1390
U$2, U$3: MOUNTINGHOLE2.5; MOUNTINGHOLE_2.5_PLATED
X4: 3.5mm Terminal; TERMBLOCK_1X3-3.5MM

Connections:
5.0V: C16.1, IC1.3 (+5V), IC3.1 (5VO)
CAN1_RX: IC1.4 (RXD), JP2.5
CAN1_S: IC1.8 (S), JP2.3
CAN1_TX: IC1.1 (TXD), JP2.4
CAN_H: IC1.7 (CANH), JP2.2, SW2.O1, X4.3
CAN_L: IC1.6 (CANL), JP2.1, SW2.O2, X4.1
GND: C1.2, C16.2, C17.2, IC1.2 (GND), IC3.2 (GND), JP2.6, X4.2
unnamed: R10.2, SW2.P1
unnamed: R11.2, SW2.P2
unnamed: C18.2, IC3.6 (C+)
unnamed: C18.1, IC3.4 (C-)
unnamed: C1.1, R10.1, R11.1
VCC: C17.1, IC1.5 (VIO), IC3.3 (~SHDN), IC3.5 (VIN), JP2.7

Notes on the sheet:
For C2, see p.7 of DS (R1xCF)

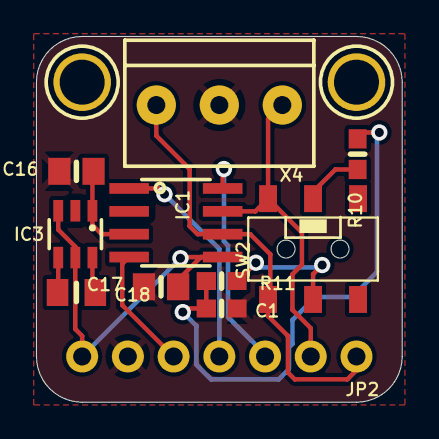
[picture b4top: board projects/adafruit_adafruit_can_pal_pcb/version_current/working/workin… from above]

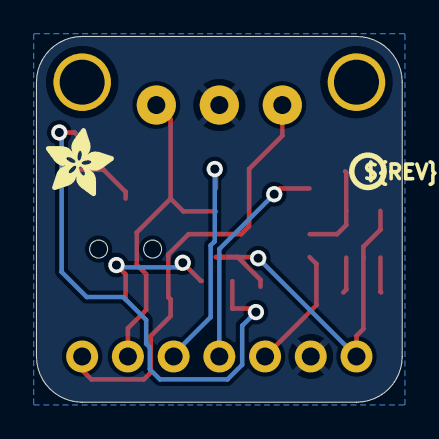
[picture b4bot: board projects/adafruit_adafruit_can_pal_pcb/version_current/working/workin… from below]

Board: 2 copper layers, 20.3 x 20.3 mm, 30 parts (5 on the bottom side), 13 nets.

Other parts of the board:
PLABEL0: PLABEL0
PLABEL1: PLABEL1
PLABEL2: PLABEL2
PLABEL3: PLABEL3
PLABEL4: PLABEL4
PLABEL5: PLABEL5
PLABEL6: PLABEL6
PLABEL7: PLABEL7
PLABEL8: PLABEL8
PLABEL9: PLABEL9
PLABEL10: PLABEL10
PLABEL11: PLABEL11
PLABEL12: PLABEL12
PLABEL13: PLABEL13
PLABEL14: PLABEL14
U$6: ADAFRUIT_3.5MM
U$7: PCBFEAT-REV-040

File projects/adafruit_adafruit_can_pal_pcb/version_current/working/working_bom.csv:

Row,Description,Part,References,Value,Footprint,Quantity Per PCB,Status,Datasheet
1,,CAP_CERAMIC0603_NO,C1,4.7nF,0603-NO,1, ,
2,,CAP_CERAMIC0805_10MGAP,C18,1uF,0805_10MGAP,1, ,
3,,CAP_CERAMIC0805-NOOUTLINE,C16 C17,10uF,0805-NO,2, ,
4,,AP3602,IC3,AP3602,SOT23-6,1, ,
5,,CAN_TRANSCIEVER_TCAN1051V,IC1,TJA1051T/3,SOIC8_150MIL,1, ,
6,,HEADER-1X770MIL,JP2,HEADER-1X770MIL,1X07_ROUND_70,1, ,
7,,RESISTOR_0603_NOOUT,R10 R11,60 ohm,0603-NO,2, ,
8,,SWITCH_DPDTEG1390,SW2,EG1390,EG1390,1, ,
9,,TERMBLOCK_1X3,X4,3.5mm Terminal,TERMBLOCK_1X3-3.5MM,1, ,





Project info:
Schematic:,working
Variant:,default
Revision:,
Date:,2023-08-02_17-08-32
KiCad Version:,7.0.6-7.0.6~ubuntu22.04.1
Statistics:
Component Groups:,9
Component Count:,11 (0 SMD/ 0 THT)
Fitted Components:,11 (0 SMD/ 0 THT)
Number of PCBs:,1
Total Components:,11
